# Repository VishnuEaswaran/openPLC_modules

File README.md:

# OpenPLC Modules

Addon modules for OpenPLC experiments.
- Traffic light - represent a 3 way traffic light 
- Motor driver for lift - circuit required for driving the motor, recieving and passing onthe limit-switch state and as an indicator showing the given logic 
- Heater/temperature control - elements to drive the reistor, which also doubles as the heating element, the cooling fan and collecting and passing on thermistor values 
- Switches - an array of a combination of NO, NC and latch switches with indicator LEDs

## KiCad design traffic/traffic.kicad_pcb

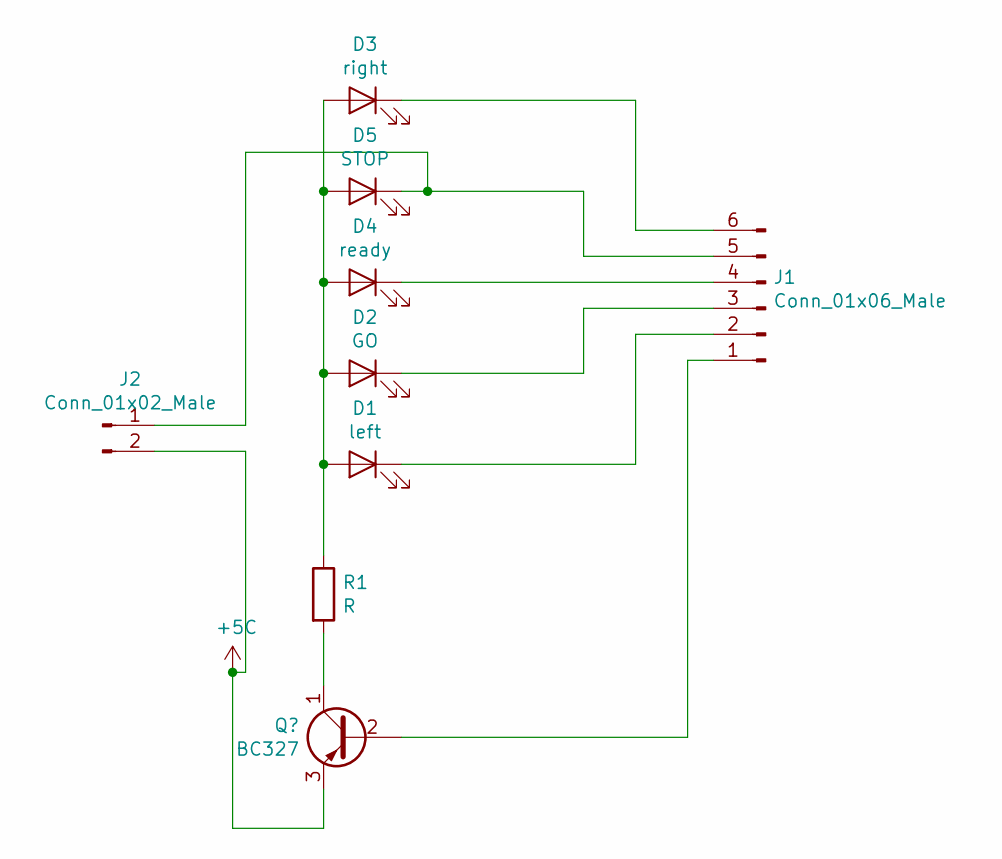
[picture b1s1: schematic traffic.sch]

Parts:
D1: left; LED_D5.0mm
D2: GO; LED_D5.0mm
D3: right; LED_D5.0mm
D4: ready; LED_D5.0mm
D5: STOP; LED_D5.0mm
J1: Conn_01x06_Male; Socket_Strip_Straight_1x06_Pitch2.54mm
J2: Conn_01x02_Male; Socket_Strip_Straight_1x02_Pitch2.54mm
R1: R; R_0603_HandSoldering

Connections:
+5C: J1.1, J2.2, R1.2
unnamed: D1.1 (K), J1.2
unnamed: D1.2 (A), D2.2 (A), D3.2 (A), D4.2 (A), D5.2 (A), R1.1
unnamed: D2.1 (K), J1.3
unnamed: D3.1 (K), J1.6
unnamed: D4.1 (K), J1.4
unnamed: D5.1 (K), J1.5, J2.1

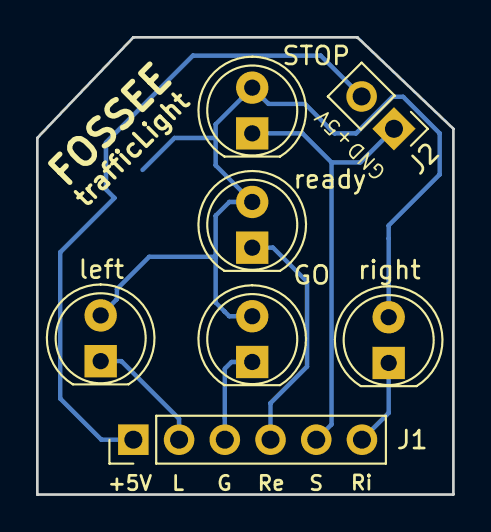
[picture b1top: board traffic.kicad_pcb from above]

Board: 2 copper layers, 23.1 x 25.4 mm, 8 parts (1 on the bottom side), 7 nets.

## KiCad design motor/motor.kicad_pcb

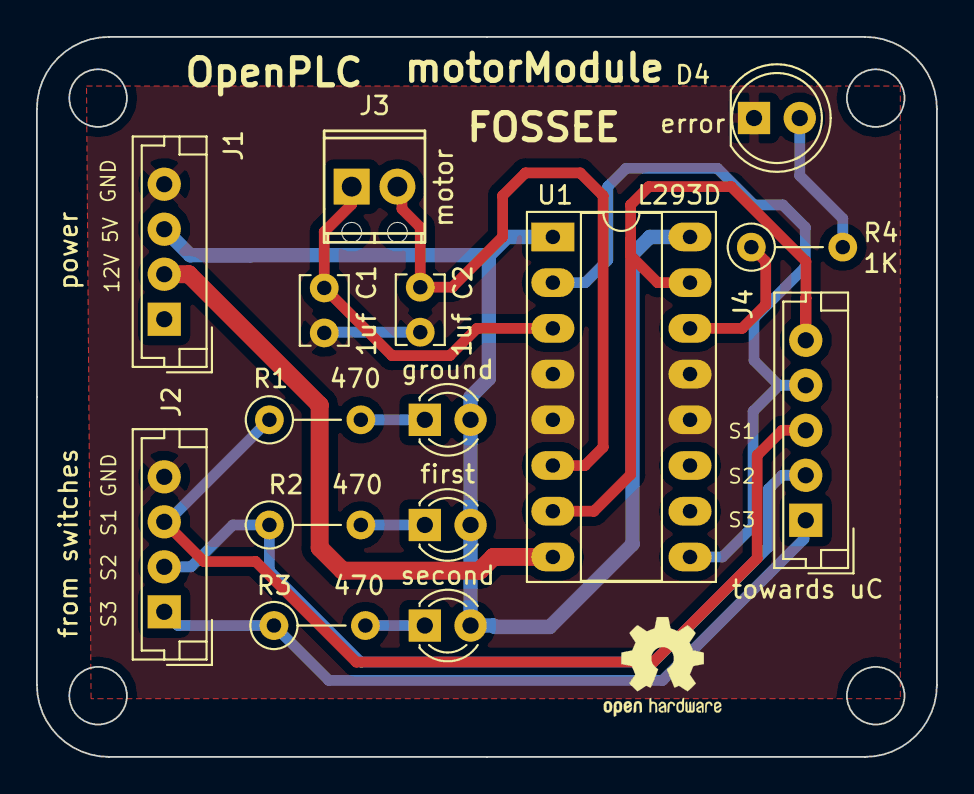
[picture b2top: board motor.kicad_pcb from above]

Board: 2 copper layers, 50.0 x 40.0 mm, 15 parts (0 on the bottom side), 15 nets.

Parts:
C1, C2: 1uf; C_Disc_D3.8mm_W2.6mm_P2.50mm
D1: ground; LED_D3.0mm
D2: first; LED_D3.0mm
D3: second; LED_D3.0mm
D4: error; LED_D5.0mm
J1: power; JST_EH_B04B-EH-A_04x2.50mm_Straight
J2: from switches; JST_EH_B04B-EH-A_04x2.50mm_Straight
J3: motor; TerminalBlock_Phoenix_MPT-2.54mm_2pol
J4: towards uC; JST_EH_B05B-EH-A_05x2.50mm_Straight
R1, R2, R3: 470; R_Axial_DIN0207_L6.3mm_D2.5mm_P5.08mm_Vertical
R4: 1K; R_Axial_DIN0207_L6.3mm_D2.5mm_P5.08mm_Vertical
U1: L293D; DIP-16_W7.62mm_Socket_LongPads

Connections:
+5V: D1.2, D2.2, D3.2, J1.3, U1.1, U1.16
+12V: J1.2, U1.8
/1a: J4.4, U1.2, U1.9
/2a: J4.5, U1.7, U1.15
/sw1: J2.3, J4.3, R1.1
/sw2: J2.2, J4.2, R2.1
/sw3: J2.1, J4.1, R3.1
GND: C1.1, C2.2, D4.1, J1.4, J2.4, U1.4, U1.5, U1.12, U1.13
unnamed: C1.2, J3.1, U1.3
unnamed: C2.1, J3.2, U1.6
unnamed: D1.1, R1.2
unnamed: D2.1, R2.2
unnamed: D3.1, R3.2
unnamed: D4.2, R4.2
unnamed: R4.1, U1.14

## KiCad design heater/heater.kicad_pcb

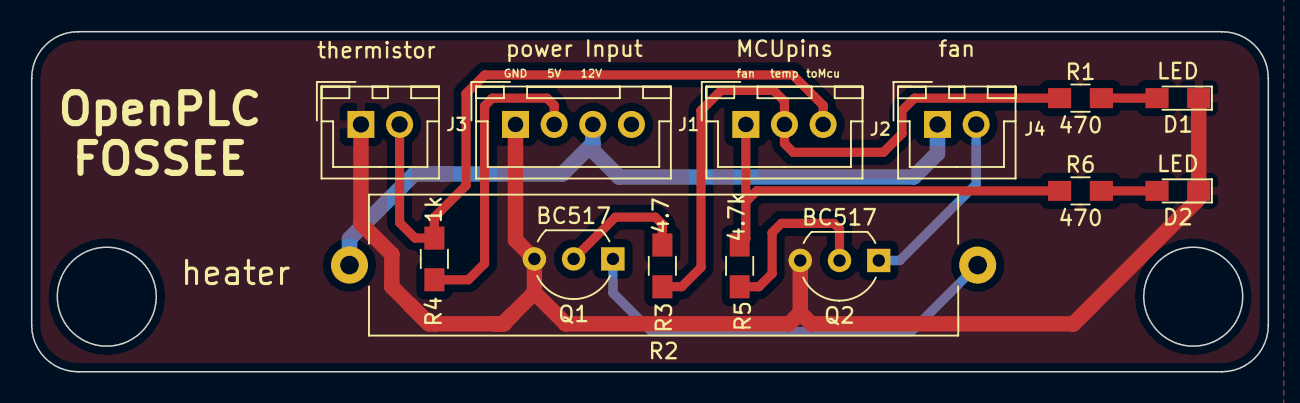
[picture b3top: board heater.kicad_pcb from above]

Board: 2 copper layers, 80.0 x 22.0 mm, 14 parts (0 on the bottom side), 12 nets.

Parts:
D1, D2: LED; LED_0805_HandSoldering
J1: power Input; JST_XH_B04B-XH-A_04x2.50mm_Straight
J2: MCUpins; JST_XH_B03B-XH-A_03x2.50mm_Straight
J3: thermistor; JST_XH_B02B-XH-A_02x2.50mm_Straight
J4: fan; JST_XH_B02B-XH-A_02x2.50mm_Straight
Q1, Q2: BC517; TO-92_Inline_Wide
R1, R6: 470; R_0805_HandSoldering
R2: 27; R_Axial_Power_L38.0mm_W9.0mm_P40.64mm
R3: 4.7; R_0805_HandSoldering
R4: 1k; R_0805_HandSoldering
R5: 4.7k; R_0805_HandSoldering

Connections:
+5V: J1.2, R4.1
+12V: J1.3, J4.1, R2.2
/fromMcuF: J2.1, R5.2, R6.1
/fromMcuR: J2.2, R1.1, R3.2
/toMcu: J2.3, J3.2, R4.2
GND: D1.1, D2.1, J1.1, J3.1, Q1.3, Q2.3
unnamed: D1.2, R1.2
unnamed: D2.2, R6.2
unnamed: J4.2, Q2.1
unnamed: Q1.1, R2.1
unnamed: Q1.2, R3.1
unnamed: Q2.2, R5.1

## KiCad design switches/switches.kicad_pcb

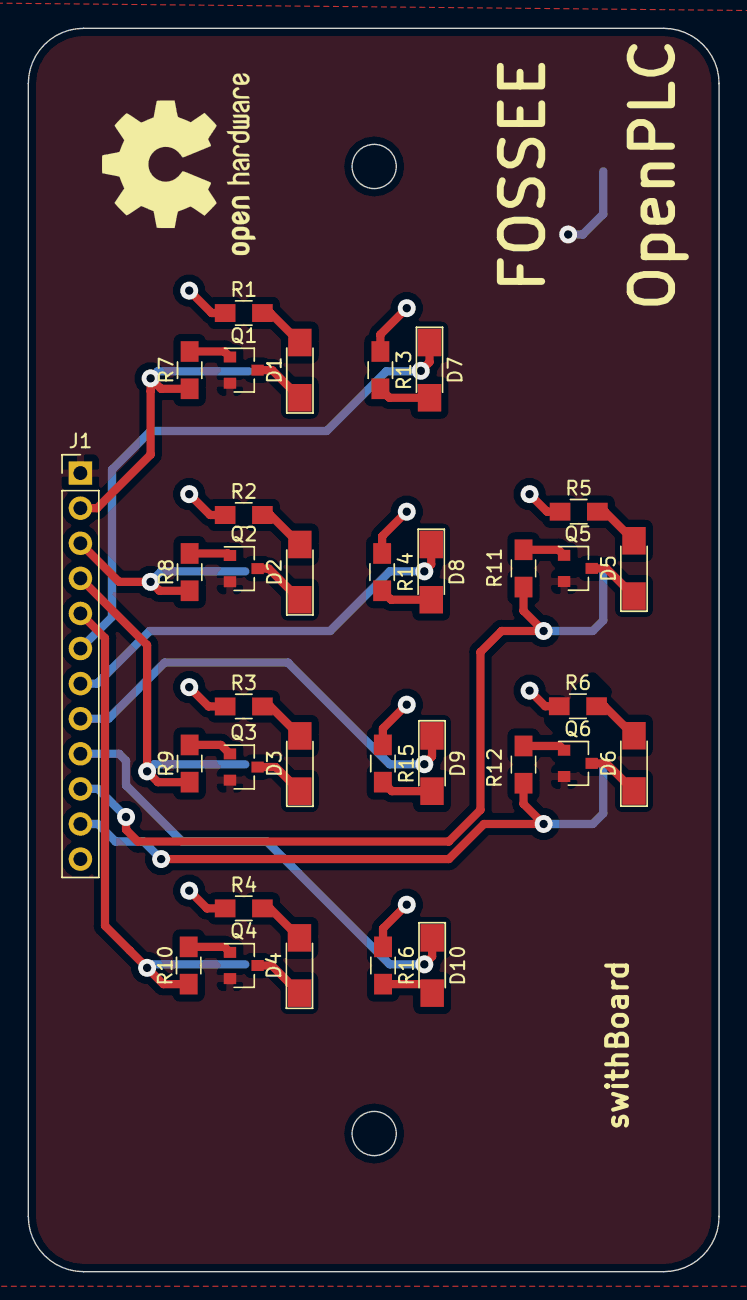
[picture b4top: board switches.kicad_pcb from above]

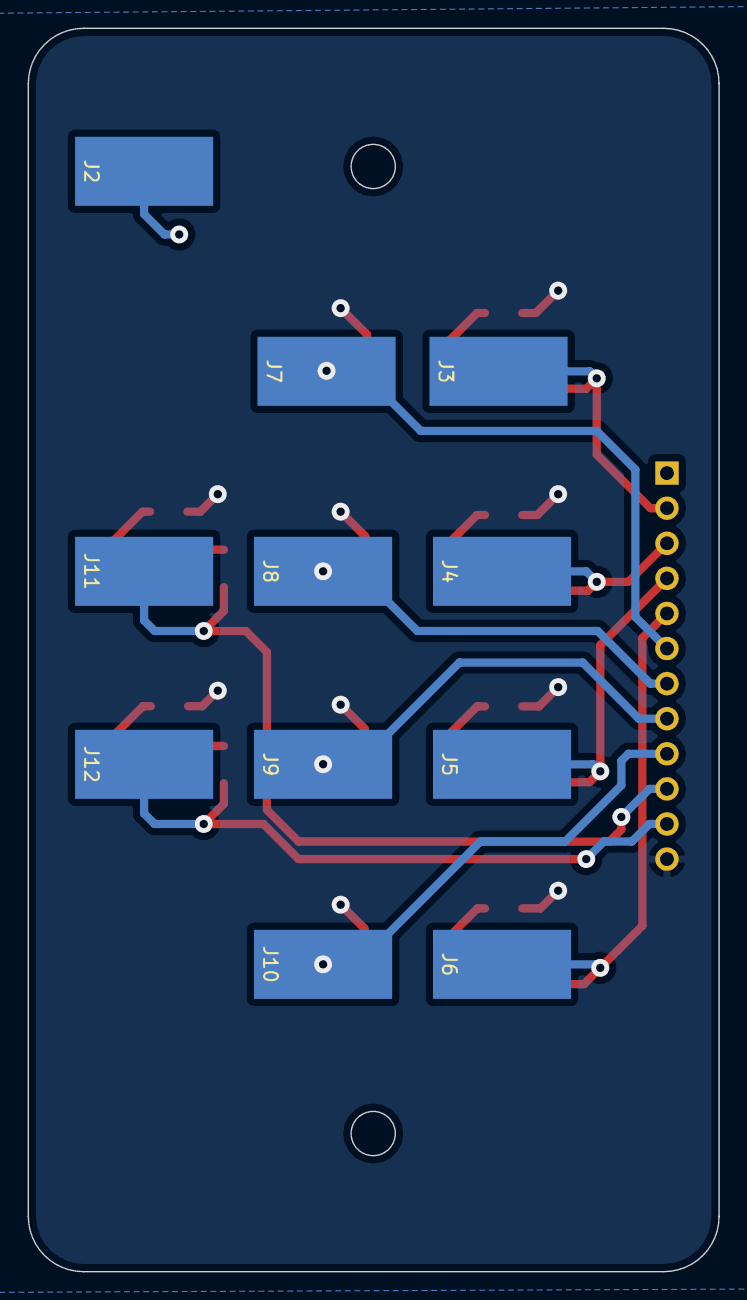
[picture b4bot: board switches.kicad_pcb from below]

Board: 2 copper layers, 50.0 x 90.0 mm, 44 parts (11 on the bottom side), 34 nets.

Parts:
D1, D2, D3, D4, D5, D6, D7, D8, D9, D10: LED; LED_1206_HandSoldering
J1: switchesOut; Socket_Strip_Straight_1x12_Pitch2.54mm
J2, J3, J4, J5, J6, J7, J8, J9, J10, J11, J12: Conn_01x01_Female; SolderWirePad_single_SMD_5x10mm
Q1, Q2, Q3, Q4, Q5, Q6: 2N7002; SOT-23
R1, R2, R3, R4, R5, R6, R7, R8, R9, R10, R11, R12, R13, R14, R15, R16: R_US; R_0805_HandSoldering

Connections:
+5V: J1.12, R1.1, R2.1, R3.1, R4.1, R5.1, R6.1, R13.1, R14.1, R15.1, R16.1
/s1: J1.2, J3.1, R7.1
/s2: J1.3, J4.1, R8.1
/s3: J1.4, J5.1, R9.1
/s4: J1.5, J6.1, R10.1
/s5: D7.1, J1.6, J7.1
/s6: D8.1, J1.7, J8.1
/s7: D9.1, J1.8, J9.1
/s8: D10.1, J1.9, J10.1
/s9: J1.10, J11.1, R11.1
/s10: J1.11, J12.1, R12.1
GND: J1.1, J2.1, Q1.2, Q2.2, Q3.2, Q4.2, Q5.2, Q6.2
unnamed: D1.1, Q1.3
unnamed: D1.2, R1.2
unnamed: D2.1, Q2.3
unnamed: D2.2, R2.2
unnamed: D3.1, Q3.3
unnamed: D3.2, R3.2
unnamed: D4.1, Q4.3
unnamed: D4.2, R4.2
unnamed: D5.1, Q5.3
unnamed: D5.2, R5.2
unnamed: D6.1, Q6.3
unnamed: D6.2, R6.2
unnamed: D7.2, R13.2
unnamed: D8.2, R14.2
unnamed: D9.2, R15.2
unnamed: D10.2, R16.2
unnamed: Q1.1, R7.2
unnamed: Q2.1, R8.2
unnamed: Q3.1, R9.2
unnamed: Q4.1, R10.2
unnamed: Q5.1, R11.2
unnamed: Q6.1, R12.2

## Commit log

2019-01-04 gti initiated and push to github
2019-01-04 Readme updated
2019-01-07 changed LEds from 3mm to 5mm;added Status LED to motor-module
2019-01-07 Heater major work done; left to design border cuts
2019-01-08 heater done
2019-01-09 added indicator LED's in heater module; added proper markings in motor module.
2019-01-10 labelled trafficLight module
2019-01-14 mounting holes in motor, extra pins in traffic, corrections in labels
2019-01-14 labels in trafficc
2019-01-14 designed and added proper cutlines for switches
2019-01-16 changed switch PCB size to 9x5 cm
2019-01-16 added a bit more description in README
2019-01-16 typos corrected in README
2019-01-17 corrected the mounting-scre-hole sizes to 3mm dia. drew symmetrical cutline for motor. updated README with new board images.
2019-01-21 created .csv bom file & also created interactive-html-bom for eac module
2019-01-22 Consolidated BOM added
2019-01-22 gerbers generate
2019-01-22 transistor driving in traffic light; updated the BOM and gerbers accordingly
2019-01-24 majorly - added port numbers; rotated 7805
2019-01-28 updated images
2019-02-26 swapped power and switch connector postions
2019-03-04 altered switches-board design; shifted resistor
2019-03-20 label correction&additions in traffic&switches modules. Updated gerbers - both V1 and modules
